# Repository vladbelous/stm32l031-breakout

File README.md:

# STM32L031x Simple Breakout

This is a simple breakout board for STM32L031K6T7 (LQFP-32) microcontroller, featuring:
* Cortex M0+ core, up to 32MHz
* 32KiB flash, 8KiB SRAM, 1KiB EEPROM

Board includes decoupling and supply capacitors, and two buttons for reset and entering bootloader.

Most pins are broken out, and extra GND pins/headers added for convenience.

STM32L-series is optimized for low power, so there's also optional:
* battery input connector (JST PH 2.0mm)
* a 2.5V LDO (AP7354 or pin-compatible)

The AP7354 has very low quiescent current (< 0.6uA), which may be useful for MCU sleeping.

Designed with KiCad 5 (www.kicad.org).

## Schematic:

## Layout:

## Toolchain setup
TODO

## Firmware uploading
TODO

## Blink example
TODO

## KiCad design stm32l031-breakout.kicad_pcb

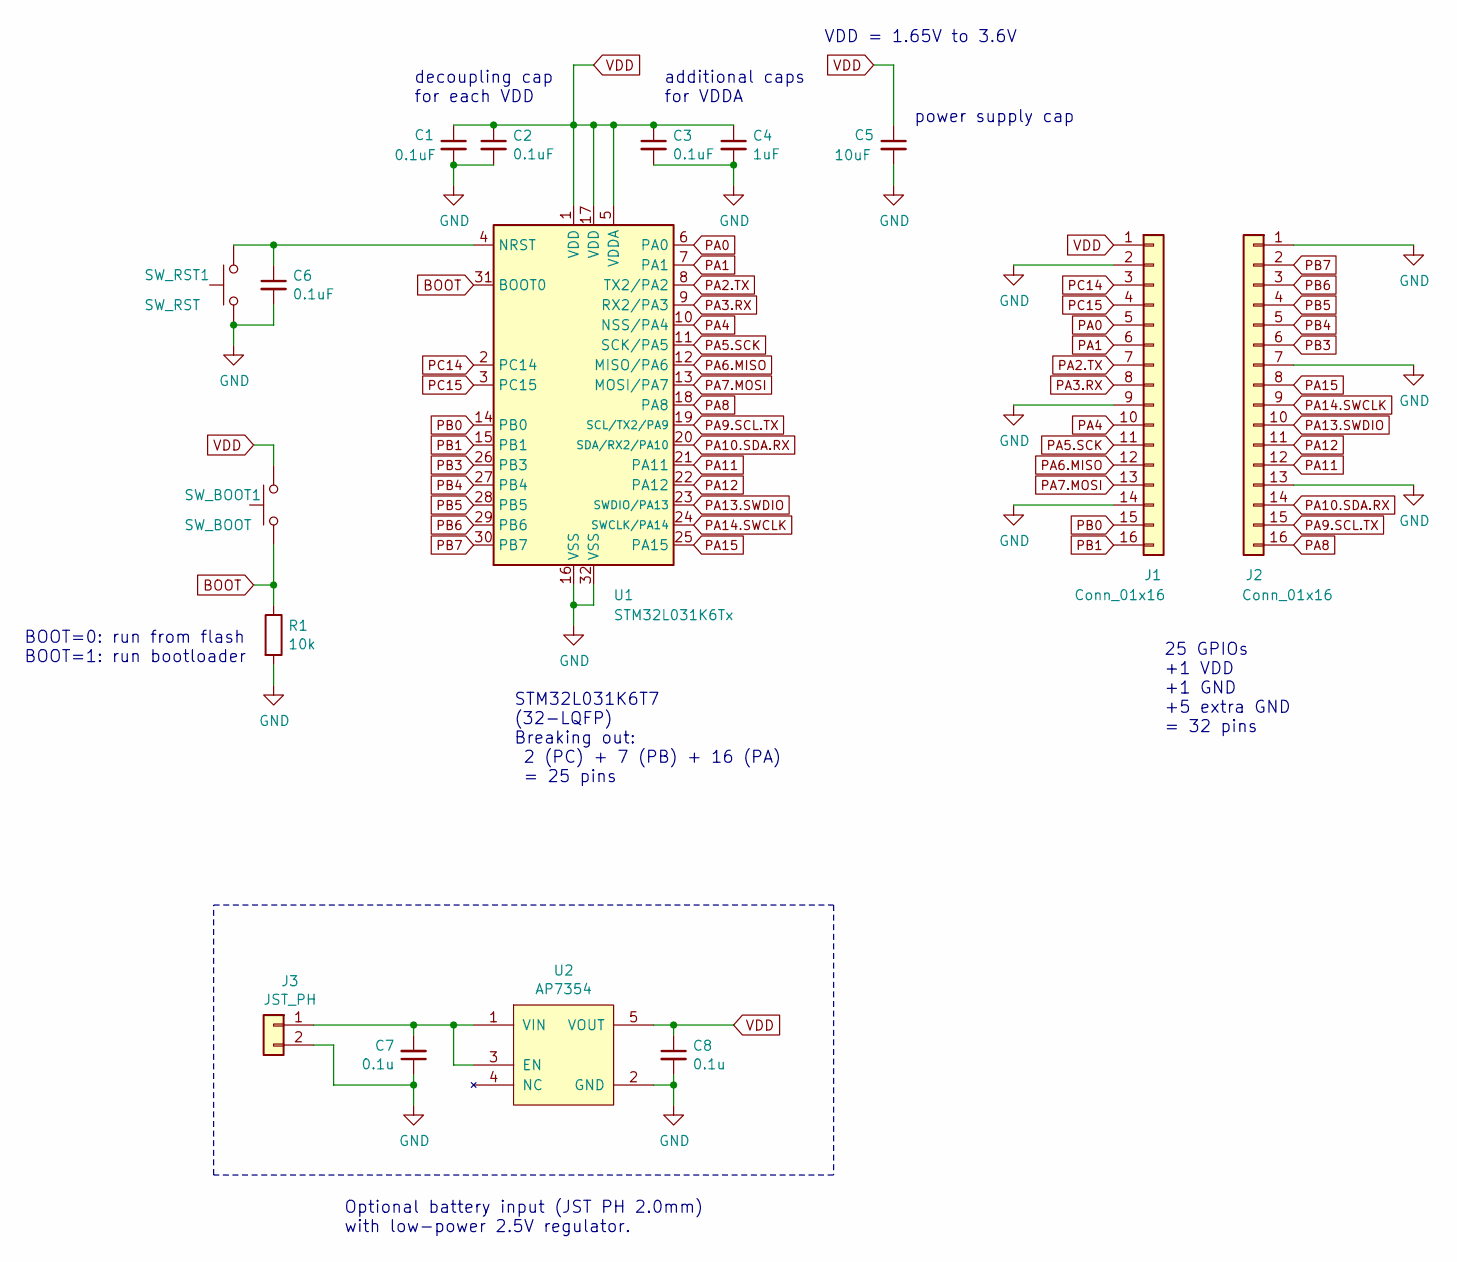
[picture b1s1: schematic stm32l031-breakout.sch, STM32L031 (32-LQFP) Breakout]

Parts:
C1, C2, C3, C6: 0.1uF; 0805_HS
C4: 1uF; 1206_HS
C5: 10uF; 1210_HS
C7, C8: 0.1u; 0805_HS
J1, J2: Conn_01x16; Pin_Header_Straight_1x16_Pitch2.54mm
J3: JST_PH; JST_PH_S2B-PH-K_02x2.00mm_Angled_WiderHole
R1: 10k; 0805_HS
SW_BOOT1: SW_BOOT; SW_SPST_PUSH_6mm_3mm
SW_RST1: SW_RST; SW_SPST_PUSH_6mm_3mm
U1: STM32L031K6Tx; TQFP-32_7x7mm_Pitch0.8mm_HS_narrow_pads
U2: AP7354; SOT-23-5_HS

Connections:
BOOT: R1.1, SW_BOOT1.1, U1.31 (BOOT0)
GND: C1.2, C2.2, C3.2, C4.2, C5.2, C6.2, C7.1, C8.2, J1.2, J1.9, J1.14, J2.1, J2.7, J2.13, J3.2, R1.2, SW_RST1.1, U1.16 (VSS), U1.32 (VSS), U2.2 (GND)
unnamed: C6.1, SW_RST1.2, U1.4 (NRST)
unnamed: C7.2, J3.1, U2.1 (VIN), U2.3 (EN)
PA0: J1.5, U1.6 (PA0)
PA1: J1.6, U1.7 (PA1)
PA2.TX: J1.7, U1.8 (TX2/PA2)
PA3.RX: J1.8, U1.9 (RX2/PA3)
PA4: J1.10, U1.10 (NSS/PA4)
PA5.SCK: J1.11, U1.11 (SCK/PA5)
PA6.MISO: J1.12, U1.12 (MISO/PA6)
PA7.MOSI: J1.13, U1.13 (MOSI/PA7)
PA8: J2.16, U1.18 (PA8)
PA9.SCL.TX: J2.15, U1.19 (SCL/TX2/PA9)
PA10.SDA.RX: J2.14, U1.20 (SDA/RX2/PA10)
PA11: J2.12, U1.21 (PA11)
PA12: J2.11, U1.22 (PA12)
PA13.SWDIO: J2.10, U1.23 (SWDIO/PA13)
PA14.SWCLK: J2.9, U1.24 (SWCLK/PA14)
PA15: J2.8, U1.25 (PA15)
PB0: J1.15, U1.14 (PB0)
PB1: J1.16, U1.15 (PB1)
PB3: J2.6, U1.26 (PB3)
PB4: J2.5, U1.27 (PB4)
PB5: J2.4, U1.28 (PB5)
PB6: J2.3, U1.29 (PB6)
PB7: J2.2, U1.30 (PB7)
PC14: J1.3, U1.2 (PC14)
PC15: J1.4, U1.3 (PC15)
VDD: C1.1, C2.1, C3.1, C4.1, C5.1, C8.1, J1.1, SW_BOOT1.2, U1.1 (VDD), U1.5 (VDDA), U1.17 (VDD), U2.5 (VOUT)

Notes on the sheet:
BOOT=0: run from flash BOOT=1: run bootloader
decoupling cap for each VDD
additional caps for VDDA
STM32L031K6T7 (32-LQFP) Breaking out: 2 (PC) + 7 (PB) + 16 (PA) = 25 pins
power supply cap
25 GPIOs +1 VDD +1 GND +5 extra GND = 32 pins
VDD = 1.65V to 3.6V
Optional battery input (JST PH 2.0mm) with low-power 2.5V regulator.

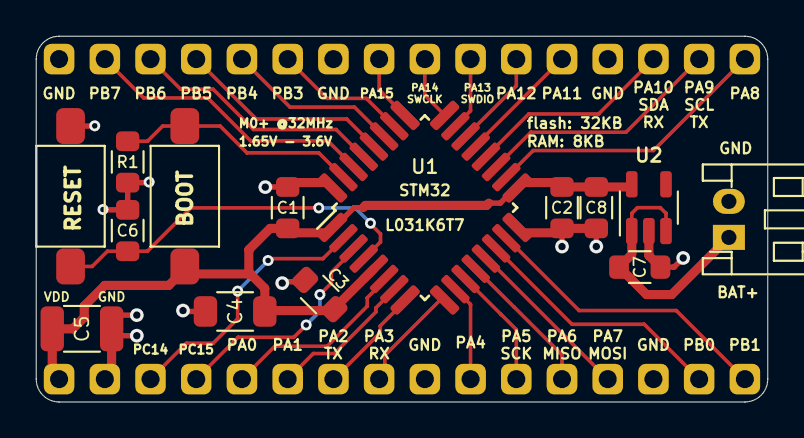
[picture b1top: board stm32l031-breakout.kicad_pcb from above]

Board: 2 copper layers, 40.6 x 20.3 mm, 16 parts (0 on the bottom side), 30 nets.

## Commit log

2019-03-21 MCU symbol
2019-03-21 Basic schematic
2019-03-21 More schematic, some footprints
2019-03-22 Complete schematic
2019-03-22 Footprint tuning, net list, initial PCB placement
2019-03-23 Placement candidate
2019-03-23 Full layout
2019-03-23 Added optional battery connector and 2V5 regulator
2019-03-25 Complete design and layout
2019-04-07 Clean-up, add README
2019-04-07 Add schematic and layout pictures
2021-11-10 Update README.md
    https://forum.kicad.info/t/warning-avoid-all-links-to-kicad-pcb-org-use-kicad-org/31521

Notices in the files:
stm32l031-breakout.kicad_pcb:
License: CC BY-SA 4.0
CC BY-SA 4.0
stm32l031-breakout.sch:
creativecommons.org/licenses/by-sa/4.0
